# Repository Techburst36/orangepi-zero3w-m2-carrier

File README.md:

# Orange Pi Zero 3W, PCIe-to-M.2 Carrier Board

Open-source KiCad design for a PCIe-to-M.2 carrier board for the Orange Pi Zero 3W (Allwinner A733). Breaks out the board's 18-pin PCIe FPC connector to an M.2 M-Key slot for NVMe storage, with an eye toward AI accelerator cards (e.g. Hailo-10H) as a longer-term stretch goal.

## Status

- Schematic: complete, ERC-clean (0 errors)
- PCB layout: complete, fully routed including differential pairs, DRC-clean (0 errors; remaining warnings are accepted and expected: 0.5mm-pitch connector solder mask clearances, deliberately downgraded to warnings, plus two harmless orphaned-geometry exclusions)
- Gerbers: exported and validated (confirmed parsing correctly on JLCPCB's quote tool, 65x32mm 2-layer board detected correctly)
- BOM: fully sourced via LCSC/JLCPCB part numbers (see below)
- **PCIe enumeration on this exact board is not yet confirmed.** As of writing, I could not find any public documentation of a PCIe device enumerating over the Zero 3W's own FPC connector specifically. That said, PCIe/NVMe has been documented working on other Allwinner A733 boards that share the same SoC and the same vendor PCIe driver, including the Orange Pi 4 Pro and the near-identical Radxa Cubie A7Z/A7A/A7S, subject to a known Gen3 enumeration bug in the vendor `sunxi-pcie` driver (Gen3 link trains but many Phison-controller NVMe drives fail to enumerate; forcing Gen1 or using a WD drive tends to work). This board exists to produce the first Zero 3W-specific test data.

**I'm not a professional electrical engineer,** this is a learning project. I've been careful and it's passed every check I know to run, but "passed DRC/ERC" is not the same as "guaranteed to work." If you can read a schematic, please review it. If something's wrong, tell me. If you have the budget to fab and test this before I do, please go for it. I'd genuinely rather someone else get the real answer sooner than have this sit unbuilt.

## Board summary

- 2-layer, 32x65mm (matches Zero 3W's own footprint and mounting hole spacing)
- Single TPS62086 buck regulator (fixed 3.3V/3A) powering the M.2 slot from the FPC connector's shared 5V rail, with added ferrite-bead input filtering
- PCIe x1 Gen1, single lane broken out (CLK, RX, TX, PERSTn, CLKREQn, WAKEn)
- GND/3V3 routed via copper pour and stitching vias; differential pairs routed same-layer via arc routing to resolve a J1/J2 pin-order mismatch

## Bill of Materials

| Ref | Part | LCSC/JLCPCB ID | Notes |
|---|---|---|---|
| U1 | TI TPS62086RLTR | C2071344 | Buck regulator, 2.5 to 6V in, fixed 3.3V/3A out |
| J1 | Molex 52746-1871 (alias of 52746-1870) | C114114 | 18-pin FPC ZIF, mates to Zero 3W's PCIe connector |
| J2 | Amphenol MDT670M01501 | C4523168 | M.2 M-Key slot, 75-pin |
| L1 | SHOU HAN CYA0630-1.0UH | C5189744 | 1uH inductor, buck stage |
| L2 | TAI-TECH HCB3216KV-501T30 | C5139915 | Ferrite bead, 5V input filtering |
| C1, C3 | Samsung CL21A106KAYNNNE | C15850 | 10uF, input and bulk |
| C2 | Samsung CL21A226MAQNNNE | C45783 | 22uF, output |

**Known supply issues at time of writing:** J1 was out of stock at JLCPCB (pre-order only). J2 had only single-digit stock remaining. Worth checking current availability before ordering, or sourcing these two from Molex/Amphenol's standard distributors (DigiKey, Mouser) directly if JLCPCB is short.

## Known open questions / issues

- **PCIe enumeration on the Zero 3W specifically is unconfirmed.** See Status above for what is and isn't known on sibling A733 boards.
- Kernel/BSP PCIe root-complex support is on the vendor Allwinner BSP kernel only; mainline Linux has no A733 PCIe controller driver yet.
- The vendor `sunxi-pcie` driver has a known Gen3 speed-change/equalization bug affecting some NVMe drives (notably Phison-controller models). Forcing the link to Gen1 via device tree, or a PCIe COMMAND-register remove/rescan fix, are the documented workarounds on sibling boards.
- GPIO 40-pin 5V power injection (for potentially powering an accelerator card back through the header) is documented as officially supported in Xunlong's manual, but not independently confirmed for stability under real accelerator load.
- Real-world total board power draw: one community data point suggests around 6.5W at 100% CPU load (untested under GPU load), against the board's rated 5V/3A (15W) ceiling. Suggests headroom exists but isn't confirmed exhaustively.

Discussion thread with more context and community replies: https://www.reddit.com/r/OrangePI/comments/1va42e7/zero_3w_building_a_custom_pcietom2_adapter/

## Repo contents

- `kicad files/`: full KiCad project (schematic, PCB, project file, design rules, library tables)
- `libraries/`: symbols, footprints, and 3D models for every part used, pre-linked to the project
- `Gerber and drill/`: exported, validated Gerber and Excellon drill files, ready for fab

## License

Released under the **CERN Open Hardware Licence v2, Permissive (CERN-OHL-P)**. This is the most open standard license for open hardware: anyone can use, build, modify, or sell this design, including for commercial purposes, without having to release their changes back. I have no plans to monetize this myself, but I'm not restricting others from building on it or selling assembled boards either. Full license text: https://ohwr.org/cern_ohl_p_v2.txt

## Contributing

Not trying to monetize or gatekeep this. If you build it, test it, find a bug, or improve on it, please open an issue or a pull request, or just reply on the Reddit thread above.

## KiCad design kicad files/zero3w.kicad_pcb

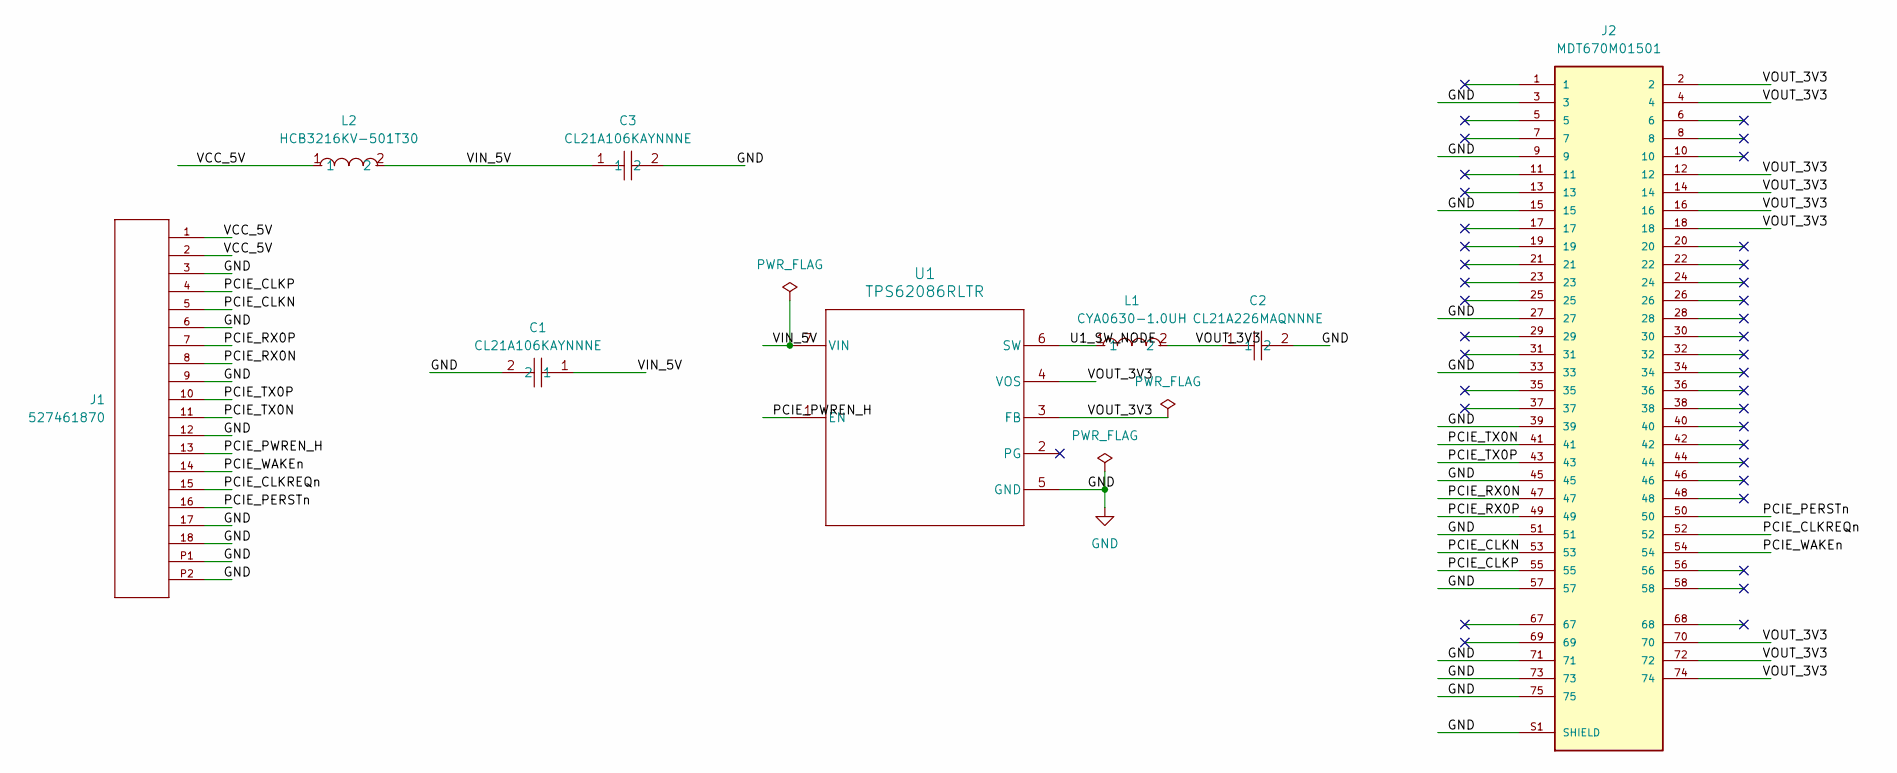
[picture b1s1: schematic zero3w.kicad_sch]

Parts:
C1, C3: CL21A106KAYNNNE; C0805; MPN CL21A106KAYNNNE; LCSC Part C15850
C2: CL21A226MAQNNNE; C0805; MPN CL21A226MAQNNNE; LCSC Part C45783
J1: 527461870; CON_527461870_MOL; MANUFACTURER_PART_NUMBER 527461870
J2: MDT670M01501; AMPHENOL_MDT670M01501; PARTREV 1
L1: CYA0630-1.0UH; IND-SMD_L7.2-W6.6_GPSR0730; MPN CYA0630-1.0UH; LCSC Part C5189744
L2: HCB3216KV-501T30; L1206; MPN HCB3216KV-501T30; LCSC Part C5139915
U1: TPS62086RLTR; RLT0007A

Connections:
/PCIE_CLKN: J1.5, J2.53
/PCIE_CLKP: J1.4, J2.55
/PCIE_CLKREQn: J1.15, J2.52
/PCIE_PERSTn: J1.16, J2.50
/PCIE_PWREN_H: J1.13, U1.1 (EN)
/PCIE_RX0N: J1.8, J2.47
/PCIE_RX0P: J1.7, J2.49
/PCIE_TX0N: J1.11, J2.41
/PCIE_TX0P: J1.10, J2.43
/PCIE_WAKEn: J1.14, J2.54
/U1_SW_NODE: L1.1, U1.6 (SW)
/VCC_5V: J1.1, J1.2, L2.1
/VIN_5V: C1.1, C3.1, L2.2, U1.7 (VIN)
/VOUT_3V3: C2.1, J2.2, J2.4, J2.12, J2.14, J2.16, J2.18, J2.70, J2.72, J2.74, L1.2, U1.3 (FB), U1.4 (VOS)
GND: C1.2, C2.2, C3.2, J1.3, J1.6, J1.9, J1.12, J1.17, J1.18, J1.P1, J1.P2, J2.3, J2.9, J2.15, J2.27, J2.33, J2.39, J2.45, J2.51, J2.57, J2.71, J2.73, J2.75, J2.S1 (SHIELD), J2.S2 (SHIELD), U1.5 (GND)

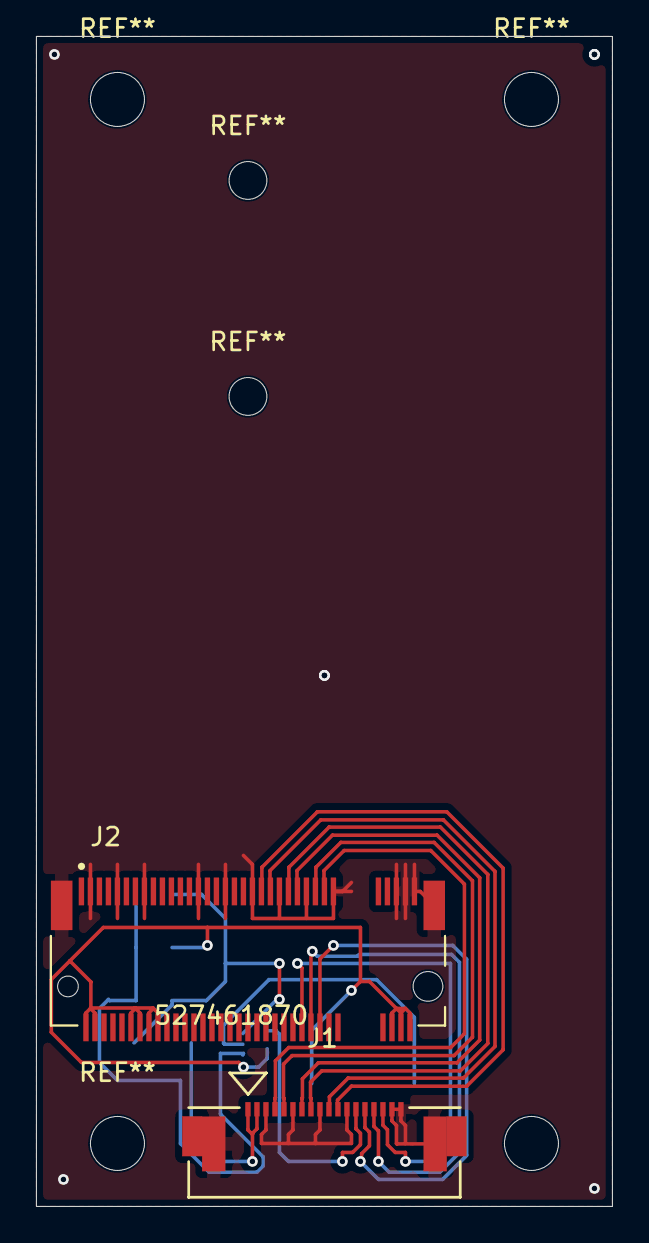
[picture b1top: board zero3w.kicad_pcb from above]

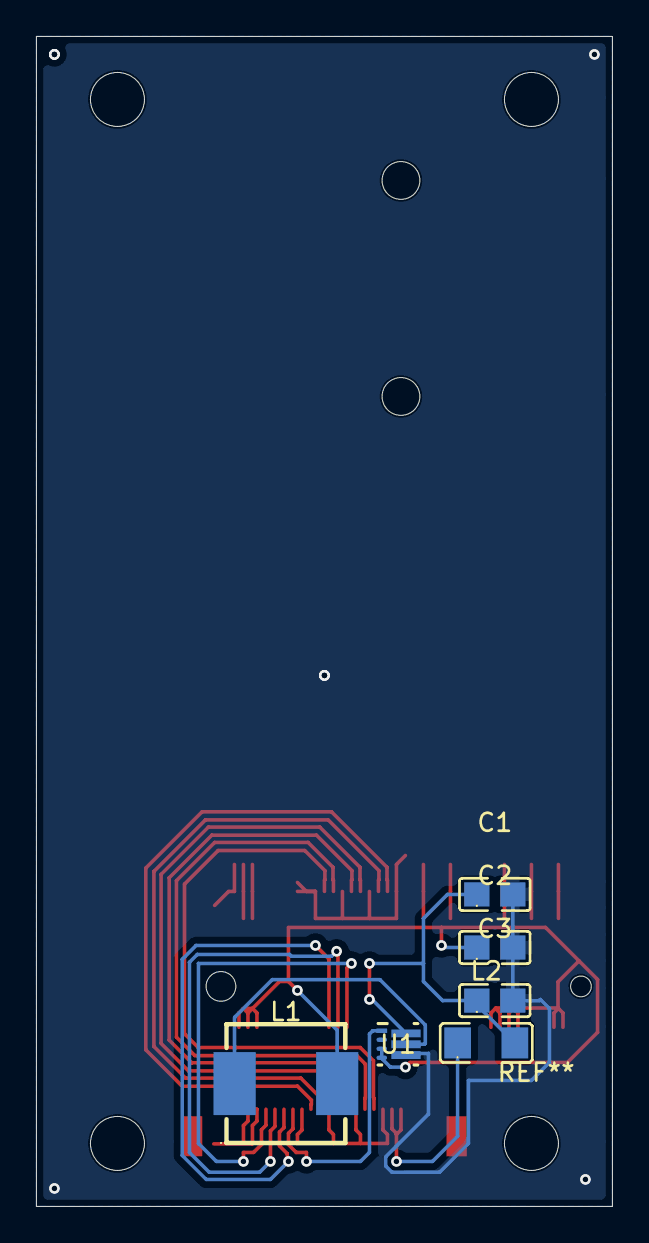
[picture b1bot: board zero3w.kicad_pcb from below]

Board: 2 copper layers, 32.0 x 65.0 mm, 8 parts (6 on the bottom side), 15 nets.
